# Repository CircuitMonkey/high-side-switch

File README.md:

# high-side-switch
P-FET based switch with TTL input for switching higher current loads on microcontrollers.

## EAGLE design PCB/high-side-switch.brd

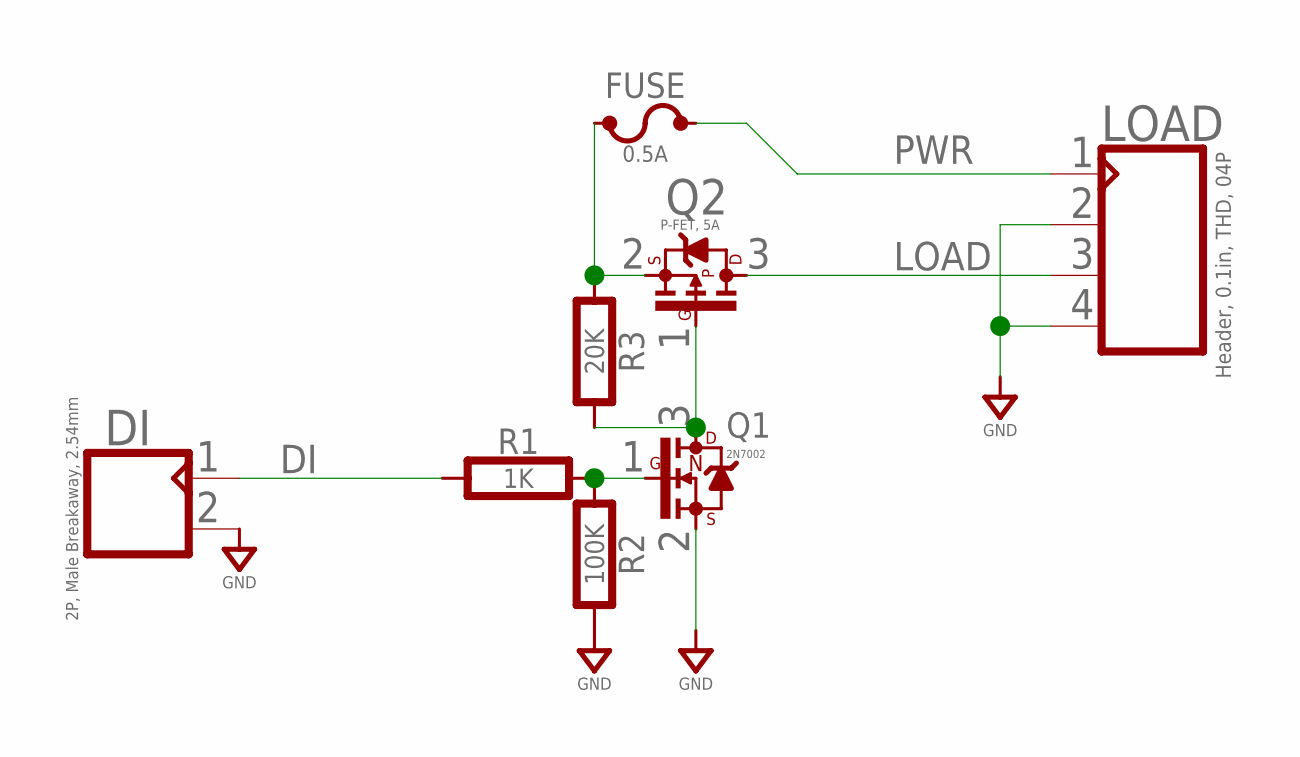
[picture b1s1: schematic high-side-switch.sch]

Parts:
DI: 2P, Male Breakaway, 2.54mm; MA02X1-VT-THD
FUSE: 0.5A; BOURNS-MF-MSMF
LOAD: Header, 0.1in, THD, 04P; MA04X1-VT-THD
Q1: 2N7002; SOT-23
Q2: P-FET, 5A; SOT-23
R1: 1K; 0603-RES
R2: 100K; 0603-RES
R3: 20K; 0603-RES

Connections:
DI: DI.1, R1.1
GND: DI.2, LOAD.2, LOAD.4, Q1.2 (S), R2.2
LOAD: LOAD.3, Q2.3 (D)
NGATE: Q1.1 (G), R1.2, R2.1
PFUSE: FUSE.2, Q2.2 (S), R3.1
PGATE: Q1.3 (D), Q2.1 (G), R3.2
PWR: FUSE.1, LOAD.1

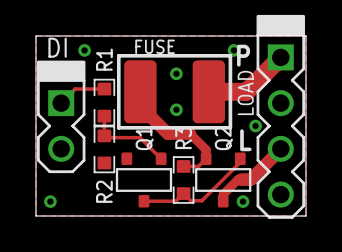
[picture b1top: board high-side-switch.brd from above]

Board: 2 copper layers, 15.0 x 10.0 mm, 8 parts (0 on the bottom side), 7 nets.

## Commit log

2022-05-01 Add PCB files for Rev.A
2022-05-01 Add images for README
2022-05-01 Update width for images in README
2022-05-01 Scaled images
2022-05-01 Add schematic image to docs and readme
2022-05-01 Create fusion sync for PCB 3D model.
